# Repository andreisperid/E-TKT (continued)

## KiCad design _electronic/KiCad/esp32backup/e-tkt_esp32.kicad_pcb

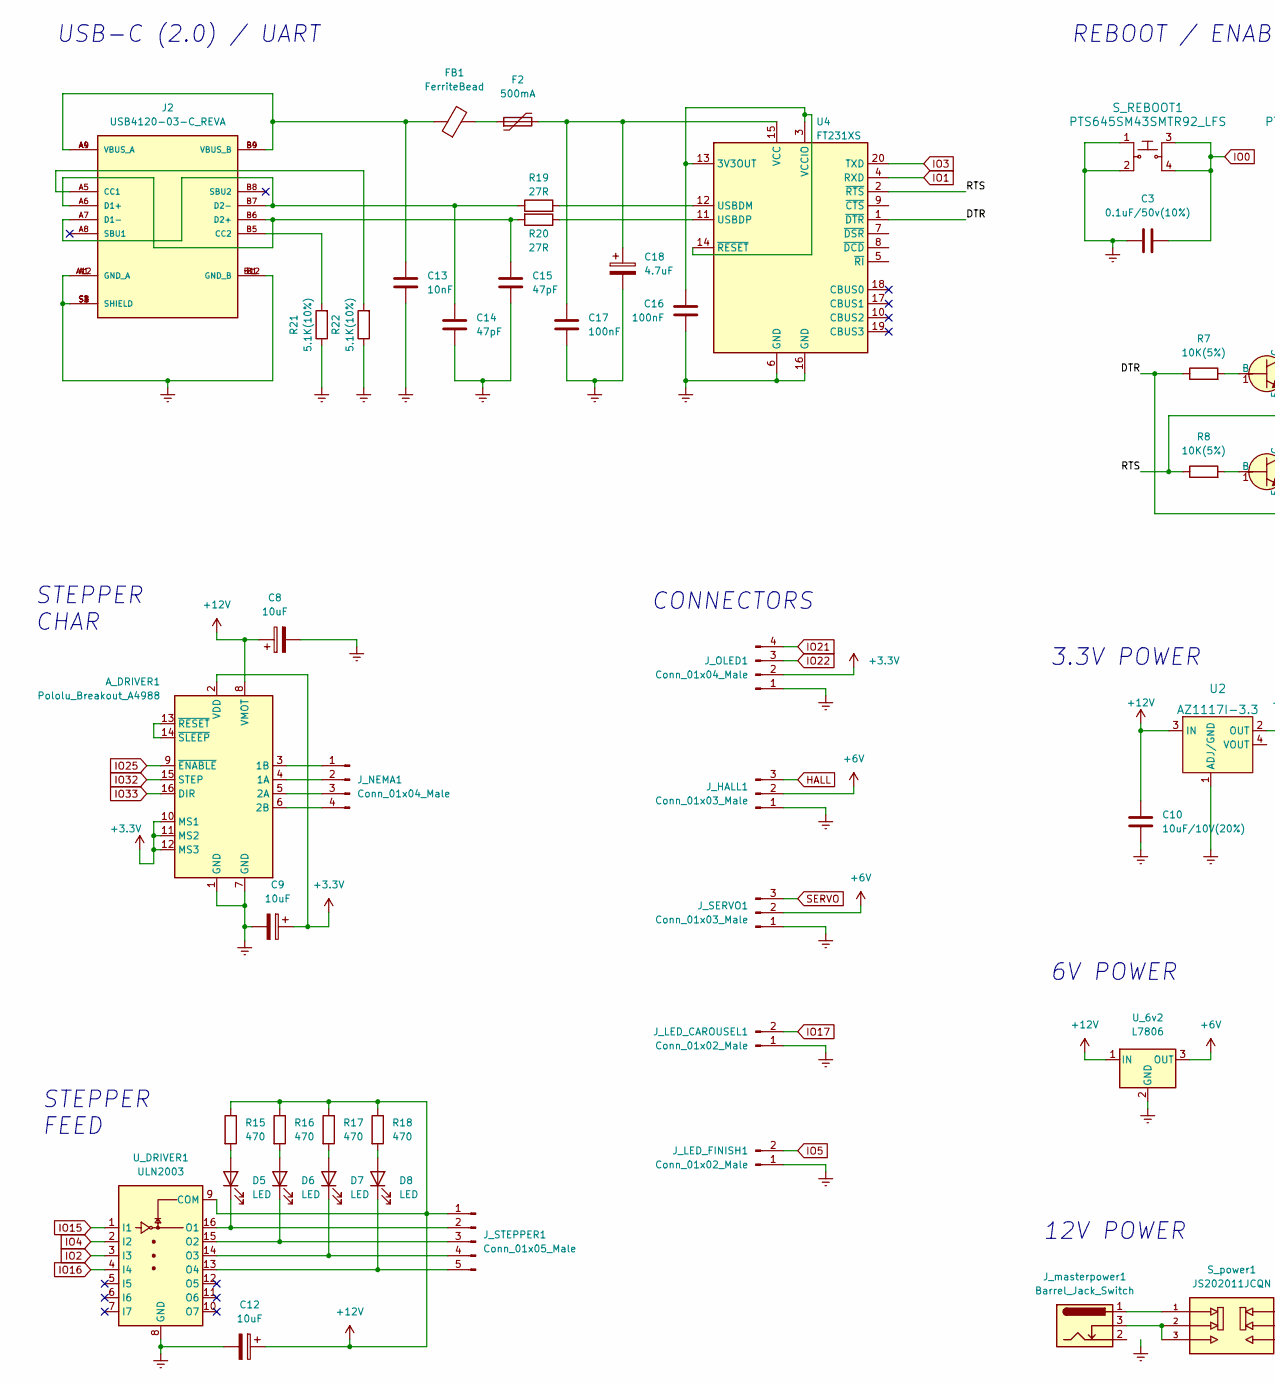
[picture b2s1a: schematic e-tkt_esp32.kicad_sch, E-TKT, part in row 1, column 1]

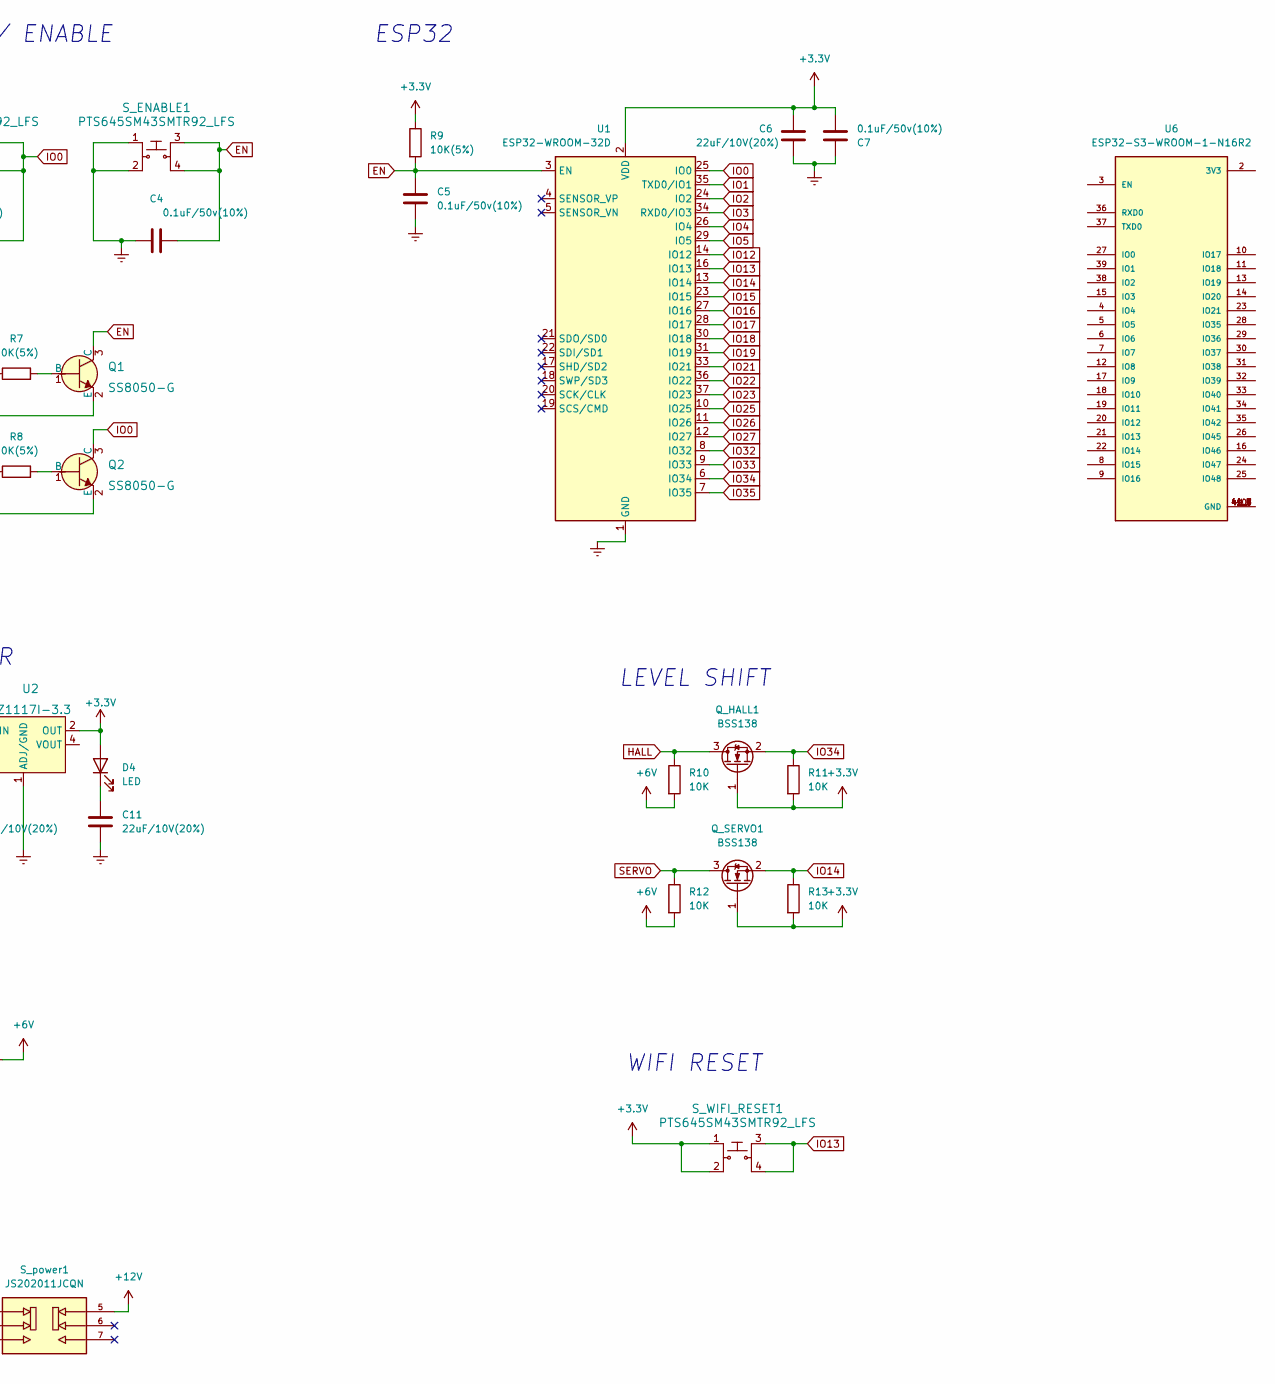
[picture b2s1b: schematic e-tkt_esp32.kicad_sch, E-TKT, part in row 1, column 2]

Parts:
A_DRIVER1: Pololu_Breakout_A4988; Pololu_Breakout-16_15.2x20.3mm
C3, C4, C5, C7: 0.1uF/50v(10%); C_0805_2012Metric
C6, C11: 22uF/10V(20%); C_0805_2012Metric
C8, C9, C12: 10uF; CP_EIA-1608-10_AVX-L
C10: 10uF/10V(20%); C_0805_2012Metric
C13: 10nF; C_0805_2012Metric
C14, C15: 47pF; C_0805_2012Metric
C16, C17: 100nF; C_0805_2012Metric
C18: 4.7uF; CP_EIA-1608-10_AVX-L
D4, D5, D6, D7, D8: LED; LED_0805_2012Metric
F2: 500mA; Fuse_1210_3225Metric
FB1: FerriteBead; L_0805_2012Metric
J2: USB4120-03-C_REVA; GCT_USB4120-03-C_REVA; PARTREV A
J_HALL1: Conn_01x03_Male; PinHeader_1x03_P2.54mm_Vertical
J_LED_CAROUSEL1: Conn_01x02_Male; PinHeader_1x02_P2.54mm_Vertical
J_LED_FINISH1: Conn_01x02_Male; PinHeader_1x02_P2.54mm_Vertical
J_NEMA1: Conn_01x04_Male; PinHeader_1x04_P2.54mm_Vertical
J_OLED1: Conn_01x04_Male; PinHeader_1x04_P2.54mm_Vertical
J_SERVO1: Conn_01x03_Male; PinHeader_1x03_P2.54mm_Vertical
J_STEPPER1: Conn_01x05_Male; PinHeader_1x05_P2.54mm_Vertical
J_masterpower1: Barrel_Jack_Switch; BarrelJack_GCT_DCJ200-10-A_Horizontal
Q1, Q2: SS8050-G; SOT-23-3; MPN MMSS8050-H-TP; Digi-Key_PN MMSS8050-H-TPMSCT-ND
Q_HALL1: BSS138; SOT-323_SC-70
Q_SERVO1: BSS138; SOT-323_SC-70
R7, R8, R9: 10K(5%); R_0805_2012Metric
R10, R11, R12, R13: 10K; R_0805_2012Metric
R15, R16, R17, R18: 470; R_0805_2012Metric
R19, R20: 27R; R_0805_2012Metric
R21, R22: 5.1K(10%); R_0805_2012Metric
S_ENABLE1: PTS645SM43SMTR92_LFS; Switch_Tactile_SMD_6x6mm_PTS645; MPN PTS645SM43SMTR92 LFS; Digi-Key_PN CKN9112CT-ND
S_REBOOT1: PTS645SM43SMTR92_LFS; Switch_Tactile_SMD_6x6mm_PTS645; MPN PTS645SM43SMTR92 LFS; Digi-Key_PN CKN9112CT-ND
S_WIFI_RESET1: PTS645SM43SMTR92_LFS; Switch_Tactile_SMD_6x6mm_PTS645; MPN PTS645SM43SMTR92 LFS; Digi-Key_PN CKN9112CT-ND
S_power1: JS202011JCQN; SW_JS202011JCQN; PARTREV 11 Nov 19
U1: ESP32-WROOM-32D; ESP32-WROOM-32
U2: AZ1117I-3.3; SOT-223; MPN AZ1117CH-3.3TRG1; Digi-Key_PN AZ1117CH-3.3TRG1DICT-ND
U4: FT231XS; SSOP-20_3.9x8.7mm_P0.635mm
U6: ESP32-S3-WROOM-1-N16R2; XCVR_ESP32-S3-WROOM-1-N16R2; PARTREV v1.0
U_6v2: L7806; TO-263-3_TabPin2
U_DRIVER1: ULN2003; SOIC-16W_5.3x10.2mm_P1.27mm

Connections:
+6V: J_HALL1.2, J_SERVO1.2, R10.2, R12.2, U_6v2.3 (OUT)
+12V: A_DRIVER1.8 (VMOT), C8.1, C10.1, C12.1, J_STEPPER1.1, R15.1, R16.1, R17.1, R18.1, S_power1.5, U2.3 (IN), U_6v2.1 (IN), U_DRIVER1.9 (COM); also elsewhere on the board
/DTR: Q2.2 (E), R7.1, U4.1 (~DTR)
/RTS: Q1.2 (E), R8.1, U4.2 (~RTS)
EN: C4.2, C5.1, Q1.3 (C), R9.2, S_ENABLE1.3, S_ENABLE1.4, U1.3 (EN)
HALL: J_HALL1.3, Q_HALL1.3 (D), R10.1
IO0: C3.2, Q2.3 (C), S_REBOOT1.3, S_REBOOT1.4, U1.25 (IO0)
IO1: U1.35 (TXD0/IO1), U4.4 (RXD)
IO2: U1.24 (IO2), U_DRIVER1.3 (I3)
IO3: U1.34 (RXD0/IO3), U4.20 (TXD)
IO4: U1.26 (IO4), U_DRIVER1.2 (I2)
IO5: J_LED_FINISH1.2, U1.29 (IO5)
IO12: U1.14 (IO12)
IO13: S_WIFI_RESET1.3, S_WIFI_RESET1.4, U1.16 (IO13)
IO14: Q_SERVO1.2 (S), R13.1, U1.13 (IO14)
IO15: U1.23 (IO15), U_DRIVER1.1 (I1)
IO16: U1.27 (IO16), U_DRIVER1.4 (I4)
IO17: J_LED_CAROUSEL1.2, U1.28 (IO17)
IO18: U1.30 (IO18)
IO19: U1.31 (IO19)
IO21: J_OLED1.4, U1.33 (IO21)
IO22: J_OLED1.3, U1.36 (IO22)
IO23: U1.37 (IO23)
IO25: A_DRIVER1.9 (~ENABLE), U1.10 (IO25)
IO26: U1.11 (IO26)
IO27: U1.12 (IO27)
IO32: A_DRIVER1.15 (STEP), U1.8 (IO32)
IO33: A_DRIVER1.16 (DIR), U1.9 (IO33)
IO34: Q_HALL1.2 (S), R11.1, U1.6 (IO34)
IO35: U1.7 (IO35)
unnamed: A_DRIVER1.3 (1B), J_NEMA1.1
unnamed: A_DRIVER1.4 (1A), J_NEMA1.2
unnamed: A_DRIVER1.5 (2A), J_NEMA1.3
unnamed: A_DRIVER1.6 (2B), J_NEMA1.4
unnamed: A_DRIVER1.13 (~RESET), A_DRIVER1.14 (~SLEEP)
unnamed: C13.2, FB1.1, J2.A4 (VBUS_A), J2.A9 (VBUS_A), J2.B4 (VBUS_B), J2.B9 (VBUS_B)
unnamed: C14.2, J2.A7 (D1-), J2.B7 (D2-), R19.1
unnamed: C15.2, J2.A6 (D1+), J2.B6 (D2+), R20.2
unnamed: C16.2, U4.3 (VCCIO), U4.13 (3V3OUT), U4.14 (~RESET)
unnamed: C17.2, C18.1, F2.2, U4.15 (VCC)
unnamed: D5.1 (K), J_STEPPER1.2, U_DRIVER1.16 (O1)
unnamed: D5.2 (A), R15.2
unnamed: D6.1 (K), J_STEPPER1.3, U_DRIVER1.15 (O2)
unnamed: D6.2 (A), R16.2
unnamed: D7.1 (K), J_STEPPER1.4, U_DRIVER1.14 (O3)
unnamed: D7.2 (A), R17.2
unnamed: D8.1 (K), J_STEPPER1.5, U_DRIVER1.13 (O4)
unnamed: D8.2 (A), R18.2
unnamed: F2.1, FB1.2
unnamed: J2.A5 (CC1), R22.2
unnamed: J2.B5 (CC2), R21.2
unnamed: J_masterpower1.1, S_power1.1
unnamed: J_masterpower1.3, S_power1.2, S_power1.3
unnamed: Q1.1 (B), R7.2
unnamed: Q2.1 (B), R8.2
unnamed: R19.2, U4.12 (USBDM)
unnamed: R20.1, U4.11 (USBDP)
unnamed: U6.1 (GND), U6.40 (GND), U6.41_1 (GND), U6.41_2 (GND), U6.41_3 (GND), U6.41_4 (GND), U6.41_5 (GND), U6.41_6 (GND), U6.41_7 (GND), U6.41_8 (GND), U6.41_9 (GND)
SERVO: J_SERVO1.3, Q_SERVO1.3 (D), R12.1

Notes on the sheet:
12V POWER
6V POWER
REBOOT / ENABLE
CONNECTORS
STEPPER CHAR
WIFI RESET
3.3V POWER
LEVEL SHIFT
STEPPER FEED
ESP32
USB-C (2.0) / UART

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
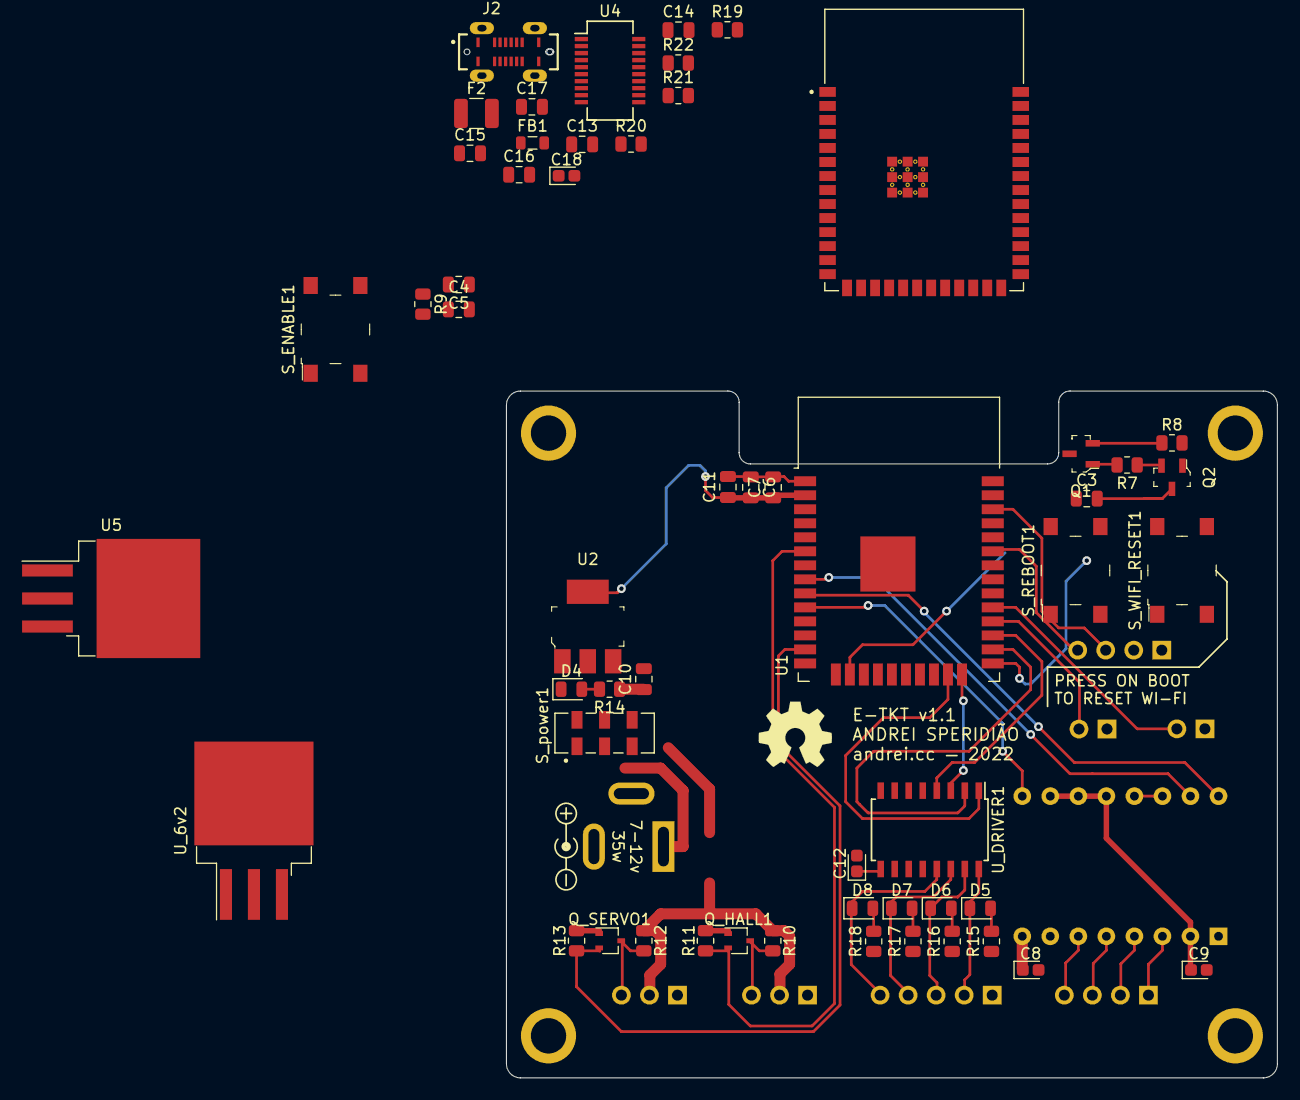
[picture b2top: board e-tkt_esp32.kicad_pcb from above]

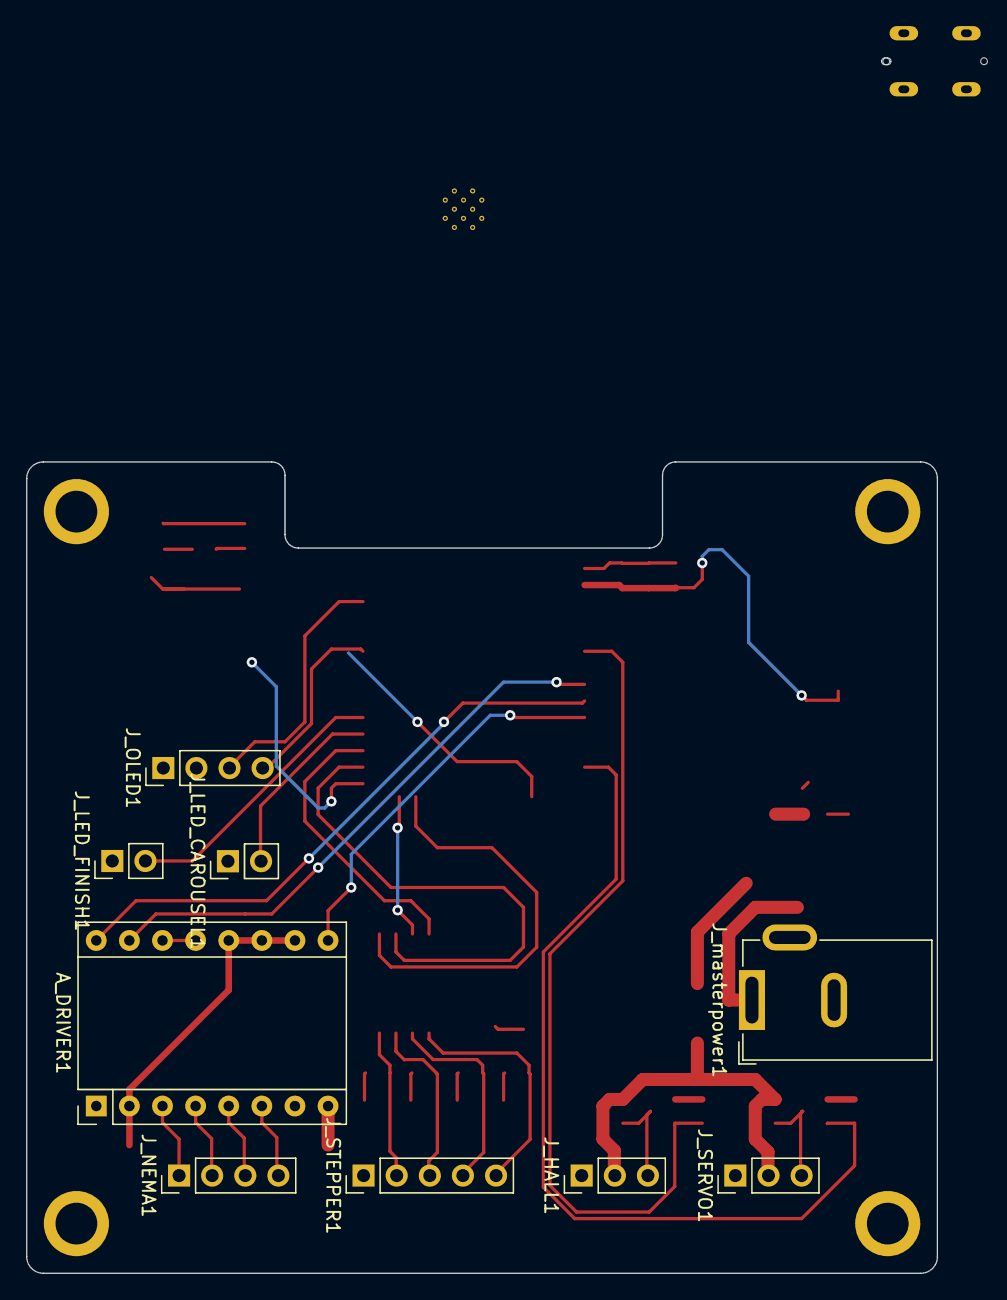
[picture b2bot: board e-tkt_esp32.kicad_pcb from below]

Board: 2 copper layers, 69.8 x 93.2 mm, 64 parts (9 on the bottom side), 55 nets.

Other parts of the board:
R14: 2K(5%); R_0805_2012Metric
U5: L7805ABD2T-TR; TO-263-3_TabPin2

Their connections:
+12V: R14.1, U5.1 (IN); also elsewhere on the board

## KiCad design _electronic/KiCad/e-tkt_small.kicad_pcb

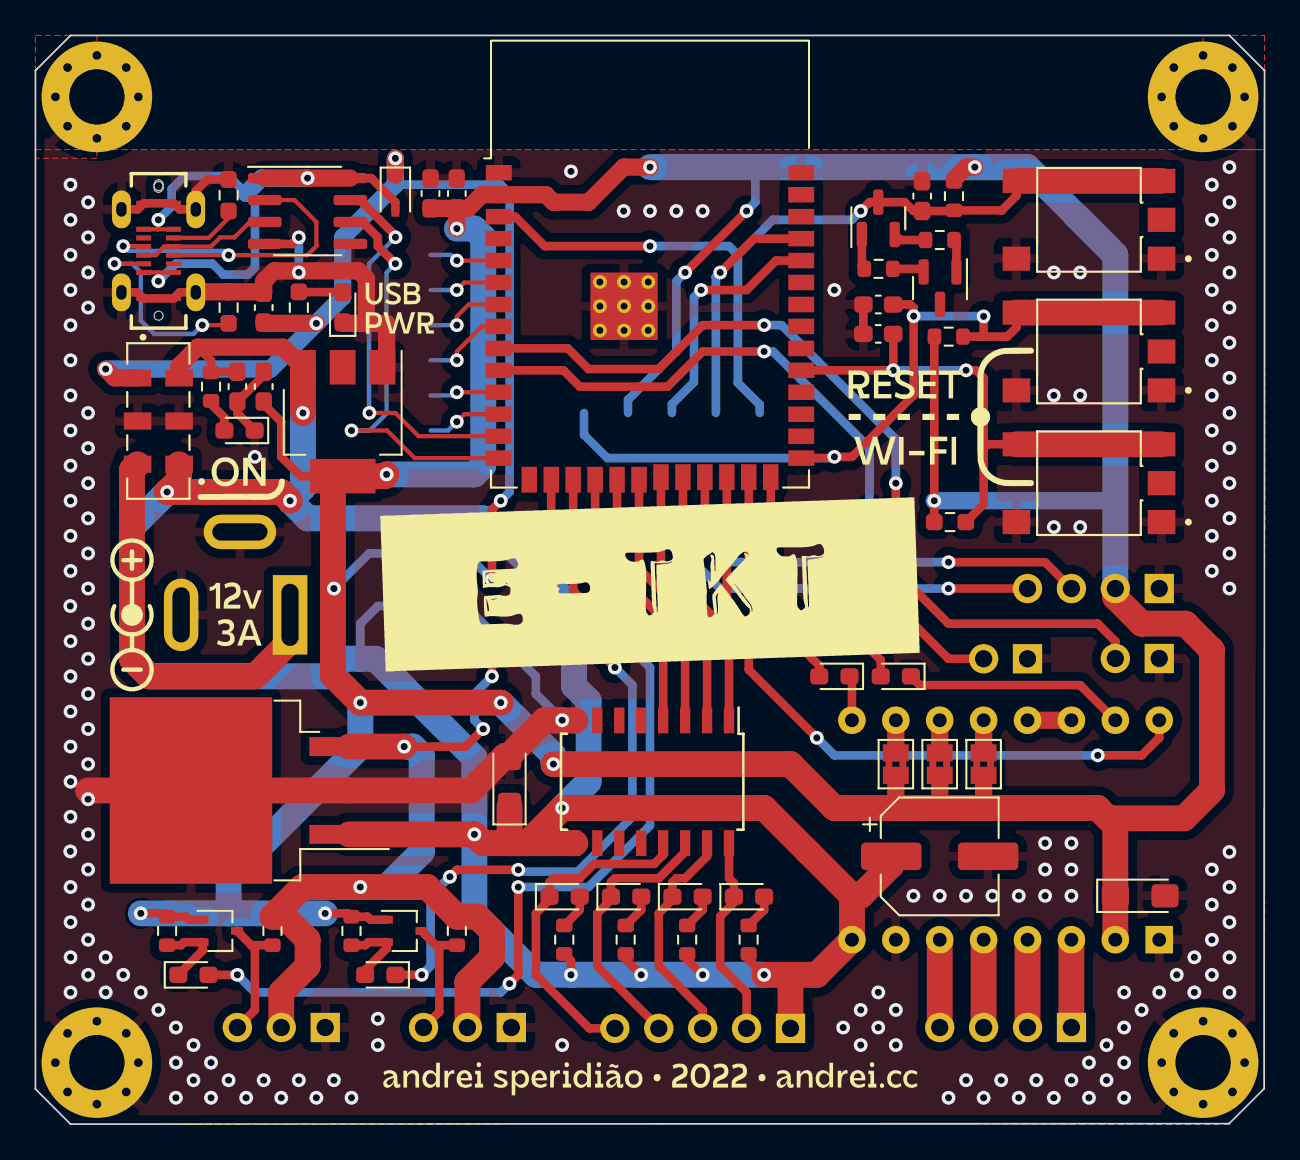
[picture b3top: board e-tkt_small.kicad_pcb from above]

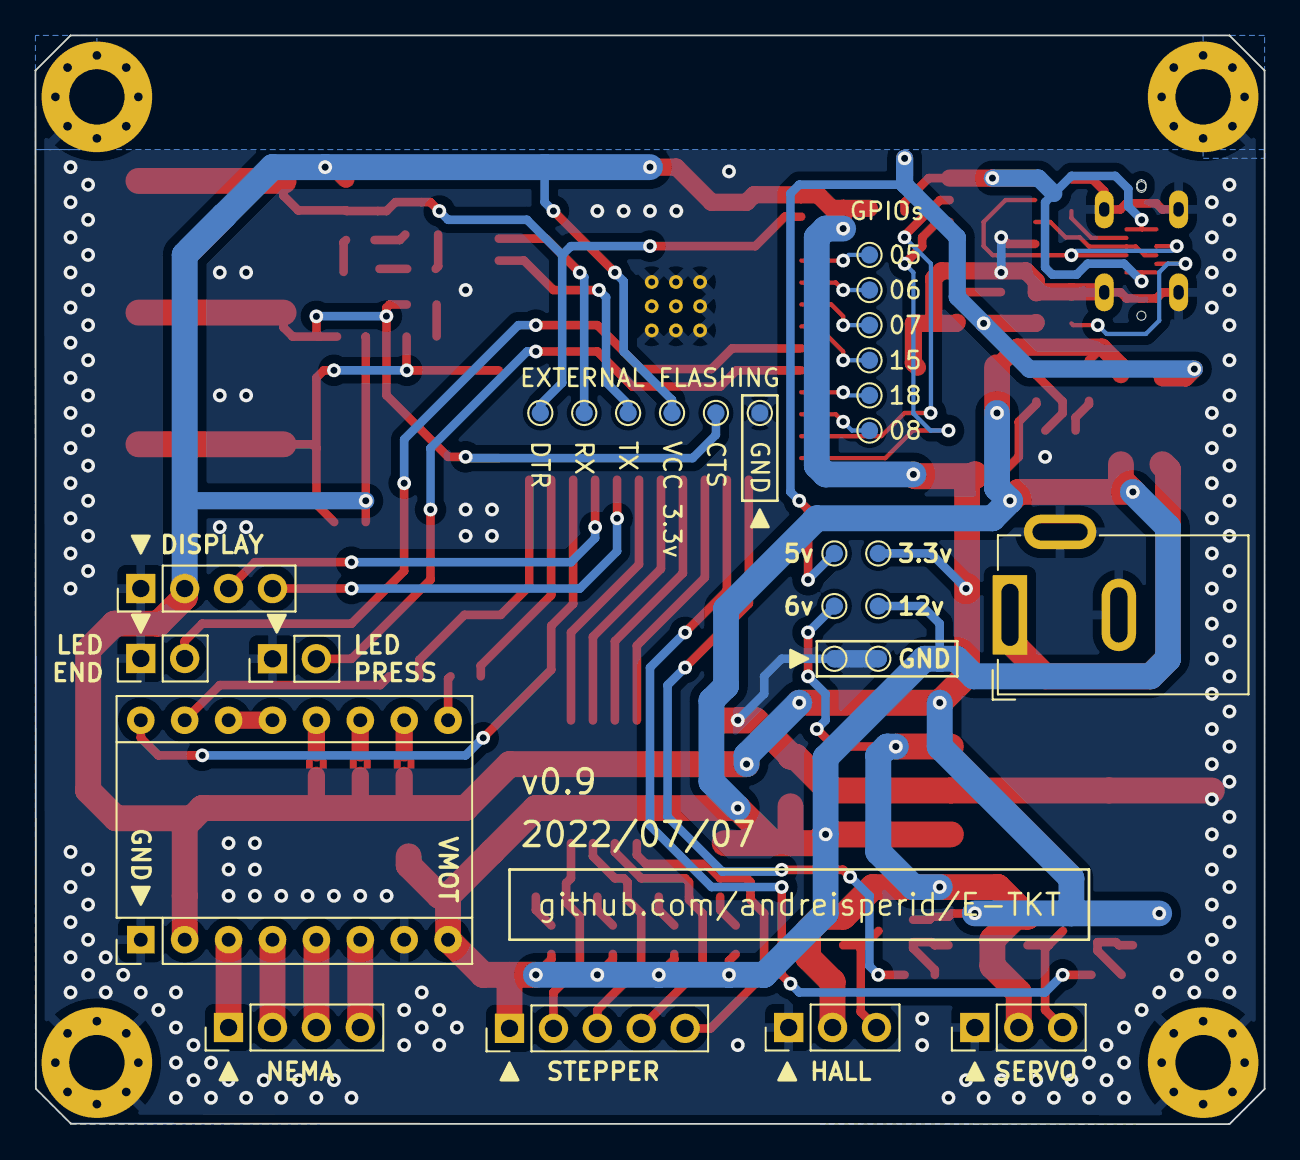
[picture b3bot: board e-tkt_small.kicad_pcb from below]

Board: 2 copper layers, 71.1 x 63.0 mm, 87 parts (27 on the bottom side), 65 nets.

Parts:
A_DRIVER1: Pololu_Breakout_A4988; Pololu_Breakout-16_15.2x20.3mm
C1, C3, C4, C7: 0.1uF/50v(10%); C_0603_1608Metric_Pad1.08x0.95mm_HandSolder
C2: 10uF/25v; C_0603_1608Metric_Pad1.08x0.95mm_HandSolder
C6, C11: 22uF/10V(20%); C_0603_1608Metric_Pad1.08x0.95mm_HandSolder
C8: 100uF; CP_Elec_6.3x5.9
C9, C12: 10uF; CP_EIA-3216-10_Kemet-I_Pad1.58x1.35mm_HandSolder
C10: 10uF/10V(20%); C_0603_1608Metric_Pad1.08x0.95mm_HandSolder
D1, D4, D5, D6, D7, D8, D9, D10, D11: LED; LED_0603_1608Metric_Pad1.05x0.95mm_HandSolder
D3: BAT760,115; D_SOD-323
D_USBIN1: LED; LED_0603_1608Metric_Pad1.05x0.95mm_HandSolder
H1, H2, H3, H4: MountingHole_Pad; MountingHole_3.2mm_M3_Pad_Via
J2: USB4120-03-C_REVA; GCT_USB4120-03-C_REVA
JP1, JP2, JP3: SolderJumper_2_Bridged; SolderJumper-2_P1.3mm_Bridged2Bar_Pad1.0x1.5mm
J_17HS4023_1: Conn_01x04_Male; PinHeader_1x04_P2.54mm_Vertical
J_28byj-48-12v_1: Conn_01x05_Male; PinHeader_1x05_P2.54mm_Vertical
J_HALL1: Conn_01x03_Male; PinHeader_1x03_P2.54mm_Vertical
J_LED_END1: Conn_01x02_Male; PinHeader_1x02_P2.54mm_Vertical
J_LED_PRESS1: Conn_01x02_Male; PinHeader_1x02_P2.54mm_Vertical
J_OLED1: Conn_01x04_Male; PinHeader_1x04_P2.54mm_Vertical
J_SERVO1: Conn_01x03_Male; PinHeader_1x03_P2.54mm_Vertical
J_masterpower1: Barrel_Jack_Switch; BarrelJack_GCT_DCJ200-10-A_Horizontal
Q1, Q2: SS8050-G; SOT-23
Q_HALL1: BSS138; SOT-323_SC-70
Q_SERVO1: BSS138; SOT-323_SC-70
R1, R5, R7, R8: 10K(5%); R_0603_1608Metric
R2, R15, R16, R17, R18: 430R; R_0603_1608Metric
R4: 10K(5%); R_0603_1608Metric_Pad0.98x0.95mm_HandSolder
R6: 100R; R_0603_1608Metric_Pad0.98x0.95mm_HandSolder
R10, R11, R12, R13: 10K; R_0603_1608Metric
R21, R22: 5.1K(10%); R_0603_1608Metric_Pad0.98x0.95mm_HandSolder
S_BOOT1: TS06-667-25-BK-100-G-SMT-TR; SW_TS06-667-25-BK-100-G-SMT-TR
S_RESET1: TS06-667-25-BK-100-G-SMT-TR; SW_TS06-667-25-BK-100-G-SMT-TR
S_WIFIRESET1: TS06-667-25-BK-100-G-SMT-TR; SW_TS06-667-25-BK-100-G-SMT-TR
S_power1: JS202011JCQN; SW_JS202011JCQN
TP_3.3v1, TP_5v1, TP_6v1, TP_12v1: TestPoint; TestPoint_Pad_D1.0mm
TP_CTS1: TestPoint; TestPoint_Pad_D1.0mm
TP_DTR1: TestPoint; TestPoint_Pad_D1.0mm
TP_GND1, TP_GND2, TP_GND3: TestPoint; TestPoint_Pad_D1.0mm
TP_IO5, TP_IO6, TP_IO7, TP_IO8, TP_IO15, TP_IO18: TestPoint; TestPoint_Pad_D1.0mm
TP_RX1: TestPoint; TestPoint_Pad_D1.0mm
TP_TX1: TestPoint; TestPoint_Pad_D1.0mm
TP_VCC_3.3V1: TestPoint; TestPoint_Pad_D1.0mm
U1: USB6B1; SOIC-8_3.9x4.9mm_P1.27mm
U2: AZ1117I-3.3; SOT-223
U3: ESP32-S3-WROOM-1-N8R2_Andrei; ESP32-S3-WROOM-1_Andrei
U_6v2: L7806; TO-263-2
U_DRIVER1: ULN2003; SOIC-16W_5.3x10.2mm_P1.27mm

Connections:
+3.3V: A_DRIVER1.2 (VDD), C6.2, C7.1, C9.1, C11.1, JP1.1 (A), JP2.1 (A), JP3.1 (A), J_OLED1.2, Q_HALL1.1 (G), Q_SERVO1.1 (G), R1.2, R4.2, R5.1, R11.2, R13.2, TP_3.3v1.1, TP_VCC_3.3V1.1, U2.2 (OUT), U2.4 (VOUT), U3.2 (3V3)
+5V: C2.2, D3.1 (K), R6.2, S_power1.7, TP_5v1.1
+6V: J_HALL1.2, J_SERVO1.2, R10.2, R12.2, TP_6v1.1, U_6v2.3 (OUT)
+12V: A_DRIVER1.8 (VMOT), C8.1, C10.1, C12.1, J_28byj-48-12v_1.1, R2.1, R15.1, R16.1, R17.1, R18.1, S_power1.1, S_power1.3, TP_12v1.1, U2.3 (IN), U_6v2.1 (IN), U_DRIVER1.9 (COM)
/D1+: J2.A6 (D1+), J2.B6 (D2+), U1.3 (I/O2)
/D1-: J2.A7 (D1-), J2.B7 (D2-), U1.2 (I/O1)
/DTR: Q2.2 (E), R7.1
/RTS: Q1.2 (E), R8.1
/VBUS_A: D3.2 (A), J2.A4 (VBUS_A), J2.A9 (VBUS_A), J2.B4 (VBUS_B), J2.B9 (VBUS_B), U1.1 (VBUS), U1.8 (VBUS)
EN: C4.2, Q1.3 (C), R1.1, S_BOOT1.2, S_BOOT1.4, TP_DTR1.1, U3.3 (EN)
GNDREF: A_DRIVER1.1 (GND), A_DRIVER1.7 (GND), C1.1, C2.1, C3.1, C4.1, C6.1, C7.2, C8.2, C9.2, C10.2, C11.2, C12.2, D11.1 (K), D_USBIN1.1 (K), H1.1, H2.1, H3.1, H4.1, J2.A1 (GND_A), J2.A12 (GND_A), J2.B1 (GND_B), J2.B12 (GND_B), J2.S1 (SHIELD), J2.S2 (SHIELD), J2.S3 (SHIELD), J2.S4 (SHIELD), J_HALL1.1, J_LED_END1.1, J_LED_PRESS1.1, J_OLED1.1, J_SERVO1.1, J_masterpower1.2, J_masterpower1.3, R21.1, R22.1, S_BOOT1.1, S_BOOT1.3, S_RESET1.1, S_RESET1.3, S_WIFIRESET1.1, S_WIFIRESET1.3, S_power1.2, S_power1.6, TP_GND1.1, TP_GND2.1, TP_GND3.1, U1.4 (GND), U1.5 (GND), U2.1 (ADJ/GND), U3.1 (GND), U3.40 (GND), U3.41 (GND), U_6v2.2 (GND), U_DRIVER1.8 (GND)
HALL: J_HALL1.3, Q_HALL1.3 (D), R10.1
IO0 RESET: C3.2, R5.2, S_RESET1.2, S_RESET1.4, TP_CTS1.1, U3.27 (IO0)
IO09: D10.2 (A), U3.17 (IO9)
IO10: U3.18 (IO10), U_DRIVER1.4 (I4)
IO11: U3.19 (IO11), U_DRIVER1.3 (I3)
IO12: U3.20 (IO12), U_DRIVER1.2 (I2)
IO13: U3.21 (IO13), U_DRIVER1.1 (I1)
IO14: J_OLED1.4, U3.22 (IO14)
IO16: J_LED_END1.2, U3.9 (IO16)
IO17: J_LED_PRESS1.2, U3.10 (IO17)
IO19 D-: U1.7 (I/O1), U3.13 (IO19)
IO20 D+: U1.6 (I/O2), U3.14 (IO20)
IO21: J_OLED1.3, U3.23 (IO21)
IO38: C1.2, R4.1, S_WIFIRESET1.2, S_WIFIRESET1.4, U3.31 (IO38)
IO45: D1.2 (A), U3.26 (IO45)
IO46: D9.1 (K), U3.16 (IO46)
IO47: A_DRIVER1.16 (DIR), U3.24 (IO47)
IO48: D4.2 (A), U3.25 (IO48)
unnamed: A_DRIVER1.3 (1B), J_17HS4023_1.1
unnamed: A_DRIVER1.4 (1A), J_17HS4023_1.2
unnamed: A_DRIVER1.5 (2A), J_17HS4023_1.3
unnamed: A_DRIVER1.6 (2B), J_17HS4023_1.4
unnamed: A_DRIVER1.9 (~ENABLE), D4.1 (K)
unnamed: A_DRIVER1.10 (MS1), JP1.2 (B)
unnamed: A_DRIVER1.11 (MS2), JP2.2 (B)
unnamed: A_DRIVER1.12 (MS3), JP3.2 (B)
unnamed: A_DRIVER1.13 (~RESET), A_DRIVER1.14 (~SLEEP)
unnamed: A_DRIVER1.15 (STEP), D1.1 (K)
unnamed: D5.1 (K), J_28byj-48-12v_1.2, U_DRIVER1.16 (O1)
unnamed: D5.2 (A), R15.2
unnamed: D6.1 (K), J_28byj-48-12v_1.3, U_DRIVER1.15 (O2)
unnamed: D6.2 (A), R16.2
unnamed: D7.1 (K), J_28byj-48-12v_1.4, U_DRIVER1.14 (O3)
unnamed: D7.2 (A), R17.2
unnamed: D8.1 (K), J_28byj-48-12v_1.5, U_DRIVER1.13 (O4)
unnamed: D8.2 (A), R18.2
unnamed: D9.2 (A), Q_HALL1.2 (S), R11.1
unnamed: D10.1 (K), Q_SERVO1.2 (S), R13.1
unnamed: D11.2 (A), R2.2
unnamed: D_USBIN1.2 (A), R6.1
unnamed: J2.A5 (CC1), R22.2
unnamed: J2.B5 (CC2), R21.2
unnamed: J_masterpower1.1, S_power1.5
unnamed: Q1.1 (B), R7.2
unnamed: Q2.1 (B), R8.2
unnamed: TP_IO5.1, U3.5 (IO5)
unnamed: TP_IO6.1, U3.6 (IO6)
unnamed: TP_IO7.1, U3.7 (IO7)
unnamed: TP_IO8.1, U3.12 (IO8)
unnamed: TP_IO15.1, U3.8 (IO15)
unnamed: TP_IO18.1, U3.11 (IO18)
RXD0: TP_TX1.1, U3.36 (RXD0)
SERVO: J_SERVO1.3, Q_SERVO1.3 (D), R12.1
TXD0: TP_RX1.1, U3.37 (TXD0)

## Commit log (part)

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2022-10-07 im the operator with my pocket calculator
2022-10-07 omit unused tone pitches
2022-10-07 adjusts on calibration
2022-10-07 alternative file for P_press 3d print
2022-10-07 documentation-specific license
2022-10-07 added licenses to software
2022-10-10 Rename heat_custom.html to head_custom.html
2022-10-13 updated stl files
2022-10-13 new 3d source file
2022-10-14 buzzer pin on new pcb
2022-10-16 removed led end on testing
2022-10-17 Rename 01_nema_stepper.md to 01_harnesses.md
2022-10-17 Rename 06_display.md to 06_feed.md
2022-10-17 Rename 07_top.md to 07_daisywheel.md
2022-10-17 Rename 01_harnesses.md to 00_harnesses.md
2022-10-17 Rename 04_chassis.md to 03_chassis.md
2022-10-17 Create 08_
2022-10-17 Rename 08_ to 08_feeder
2022-10-17 Rename 08_feeder to 08_feeder.md
2022-10-17 fixed wrong hall header on pcb
2022-10-18 fixed hall header on pcb
2022-10-18 removed old electronic files
2023-01-01 Use lowercase for the font file name as the webserver expects
2023-01-11 Make some hardware parameters configurable
2023-01-14 Move UI state handling into the webserver
2023-01-15 Undo accidental change to default serial settings
2023-02-08 separate file for optional config (hall/direction)
2023-02-08 improved code visibility for opt config
2023-02-08 configured gitignore for optional config
2023-02-08 fixed 99% progress when beginning printing
2023-02-17 Note the prevChar is changed during homing
    Otherwise the printer can print the wrong character at the start of a print
2023-02-17 Make input elements selectable
    This is necessary to make UI elements work on safari mobile. Other browsers are suspiciously unaffected despite how that CSS is supposed to work.
2023-03-12 Support UTF8 and scroll for longer label text
2023-03-20 fixes 'char' to 'const char*' convertion error
2023-03-20 form button labels not selectable anymore
2023-03-30 Make settings use the correct task endpoint
2023-03-30 Add a server that simulates a physical E-TKT
2023-04-12 Update bom.md
    Added proper spec names for fasteners and replaced 2 rotted links with generic search links
2023-04-13 Update bom.md
    Replaced rotted links with new ones or search links (the servo is currently only available as multiple).
    Also added an example for the power brick.
2023-04-13 Add PCB specs to electronics.md
    Add PCB specs for people that don't know what to enter when ordering PCBs.
2023-04-16 Correct OLED control chip designation
    Accidentally added wrong chip designation in previous commit.
2023-04-19 add separated 3D STEP files, by layer
2023-04-19 updated step files, m3x16 side screws
2023-04-19 updated stl files, m3x16 side screws
2023-04-19 remove backup files
2023-04-20 added first version of custom pressWheel
2023-04-21 scrolling text input
2023-04-24 improved custom wheel test
2023-04-24 adjusted custom wheel parameters
2023-04-24 tips beside text input when scrolled mid way
2023-04-24 cross-browser scrollbars and some QOL improvements
    I've added a bunch of logic to handle different browser eccentricities:
    - I've verified that iOS never displays a scrollbar, which I suppose iOS users are comfortable with.
    - I've added lots of fancy CSS selectors to make the scrollbars as visually consistent on firefox desktop and mobile as possible. This is accomplished by adding a ```position: sticky``` element insid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
    I also made a number of other quality-of-life
2023-04-25 Remove sources of layout height shifting
2023-04-25 added a section cut option to help with tuning
2023-04-25 closed the small gaps at bottom disc center
2023-04-25 embHght represents the char height again
2023-04-25 introduced option to show the positives in the topwheel to better see spacing spacings are now selectable for XY and Z separately
2023-04-25 added option to render labels to the top disc
2023-04-25 started experimenting with fonts
2023-04-25 created module for 16segment display
2023-04-25 preparations for presets
2023-04-25 Update pressWheel.scad
    user can now select to create a 16-segment inspired wheel. Letters and numbers needs to be combined by multiple presses without feeding the tape.
2023-04-25 limits the number of musical tones to 16
2023-04-25 limits the input characters to approx. 1 meter
2023-04-25 jumping to text scroll start and end
2023-04-28 Speed up the song for long labels
2023-04-28 Add hover to scroll tips, and hide when printing
2023-04-29 Configure optional OTA updates
2023-04-29 Revert some accidentally submitted #define changes
2023-04-29 Sync print progress across browser sessions
2023-05-02 Break out firmware into multiple classes.
2023-05-03 Fix progress reporting (webapp and firmware)
2023-05-03 Properly handle printer busy error
2023-05-03 Add monitoring for uptime and memory
2023-05-03 rename from Carousel to DaisyWheel
2023-05-03 standardized some header descriptions
2023-05-04 fixes the LEDs behavior
2023-05-04 disables autofill keyboard bar on input
